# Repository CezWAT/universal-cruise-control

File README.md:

Universal cruise control for cars

# What it is
This project is about to bring cruise control to my Fiat 126p, but basically it should be possible to adapt it to any car.

# Sensors used
- hall sensor as a speed sensor
- brake light switch (already in place)
- clutch switch (has to be added)
- Three buttons (+, -, cancel)

# What is driving what
Based on the speed sensor, the device regulates PWM signal with PI loop. It tries to keep the vehicle speed as close as possible to the one set with the buttons. What controls the engine is a simple, but "strong" servomotor. In my case it is TiankongRC TD-6620MG (they say it has metal gears, 180 degrees of movement and 20 kg of torque). The servo is attached to gas pedal linkage as it is a simple connection and there are no vibrations on the floor compared to the engine.

# Where is the firmware
In FW directory. Be aware, that for now it is only a proof of concept made for HW v. 1. There are many functions that I would like to work but I didn't code it yet.

It's bare metal and I started writing it with HW v1, so I have to make some changes.

# Changes in HW between versions
v1:
- controls DC motor with H bridge. It came out as not so simple due to lack of motor position sensing.
- buttons and switches had to be debounced in code, this takes time and control over cruise control is somehow critical on the road.
- buttons were driven from the VCC.
- I misplaced pins in AMSR20783.3JZ footprint.

v2:
- improved misconceptions from above.
- JST connectors instead of goldpins.
- improved routing and footprints (for example SOT123 in place of SOT323 for improved solderability).

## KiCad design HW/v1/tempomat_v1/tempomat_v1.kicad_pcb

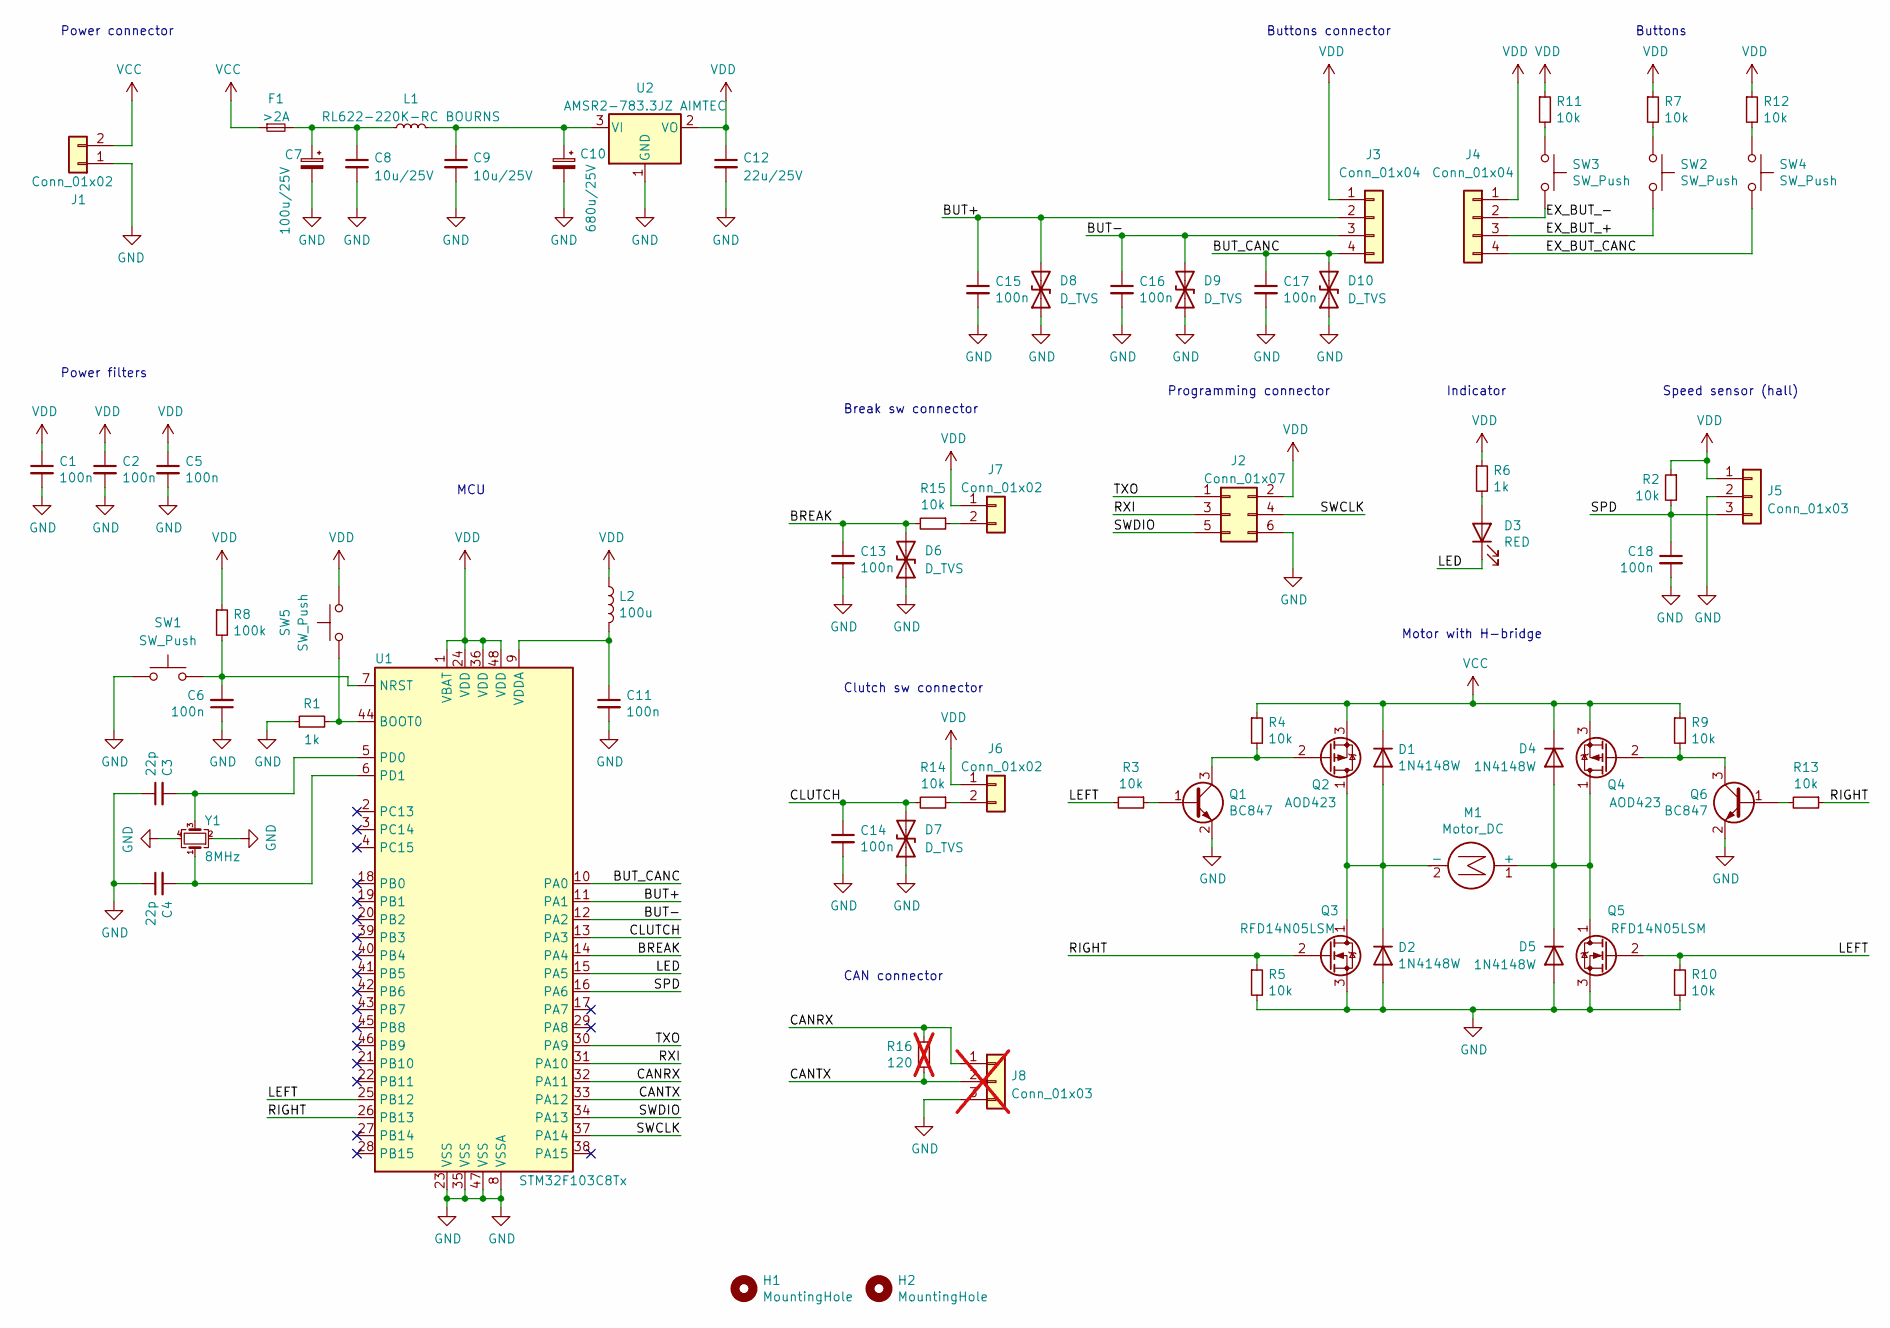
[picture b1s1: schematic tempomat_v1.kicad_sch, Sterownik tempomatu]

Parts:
C1, C2, C5, C6, C13, C14, C15, C16, C17, C18: 100n; C_0603_1608Metric
C3, C4: 22p; C_0603_1608Metric
C7: 100u/25V; CP_Radial_D5.0mm_P2.50mm
C8, C9: 10u/25V; C_1206_3216Metric
C10: 680u/25V; CP_Radial_D10.0mm_P5.00mm
C11: 100n; C_0603_1608Metric_Pad1.08x0.95mm_HandSolder
C12: 22u/25V; CP_Radial_D6.3mm_P2.50mm
D1, D2, D4, D5: 1N4148W; D_SOD-123
D3: RED; D_0603_1608Metric
D6, D7, D8, D9, D10: D_TVS; D_SOD-323_HandSoldering
F1: >2A; Fuse_0805_2012Metric
H1, H2: MountingHole; MountingHole_3.5mm
J1: Conn_01x02; TerminalBlock_bornier-2_P5.08mm
J2: Conn_01x07; PinHeader_2x03_P2.54mm_Vertical
J3, J4: Conn_01x04; PinHeader_1x04_P2.54mm_Vertical
J5: Conn_01x03; PinHeader_1x03_P2.54mm_Vertical
J6, J7: Conn_01x02; PinHeader_1x02_P2.54mm_Vertical
J8: Conn_01x03; PinHeader_1x03_P2.54mm_Vertical; not fitted
L1: RL622-220K-RC BOURNS; L_Radial_D8.7mm_P5.00mm_Fastron_07HCP
L2: 100u; L_1210_3225Metric_Pad1.42x2.65mm_HandSolder
M1: Motor_DC; PinHeader_1x02_P2.54mm_Vertical
Q1, Q6: BC847; SOT-23
Q2, Q4: AOD423; TO-252-3_TabPin1
Q3, Q5: RFD14N05LSM; TO-252-3_TabPin1
R1, R6: 1k; R_0603_1608Metric
R2, R3, R4, R5, R7, R9, R10, R11, R12, R13, R14, R15: 10k; R_0603_1608Metric
R8: 100k; R_0603_1608Metric
R16: 120; R_0603_1608Metric; not fitted
SW1, SW2, SW3, SW4, SW5: SW_Push; SW_PUSH_6mm
U1: STM32F103C8Tx; LQFP-48_7x7mm_P0.5mm
U2: AMSR2-783.3JZ AIMTEC; AMSR2-78JZ
Y1: 8MHz; Crystal_SMD_EuroQuartz_MJ-4Pin_5.0x3.2mm

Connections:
/BREAK: C13.1, D6.2 (A2), R15.2, U1.14 (PA4)
/BUT+: C15.1, D8.2 (A2), J3.2, U1.11 (PA1)
/BUT-: C16.1, D9.2 (A2), J3.3, U1.12 (PA2)
/BUT_CANC: C17.1, D10.2 (A2), J3.4, U1.10 (PA0)
/CANRX: J8.1, R16.1, U1.32 (PA11)
/CANTX: J8.2, R16.2, U1.33 (PA12)
/CLUTCH: C14.1, D7.2 (A2), R14.2, U1.13 (PA3)
/EX_BUT_+: J4.3, SW2.2
/EX_BUT_-: J4.2, SW3.2
/EX_BUT_CANC: J4.4, SW4.2
/LED: D3.1 (K), U1.15 (PA5)
/LEFT: Q5.2 (G), R3.2, R10.1, U1.25 (PB12)
/RIGHT: Q3.2 (G), R5.1, R13.1, U1.26 (PB13)
/RXI: J2.3, U1.31 (PA10)
/SPD: C18.1, J5.3, R2.2, U1.16 (PA6)
/SWCLK: J2.4, U1.37 (PA14)
/SWDIO: J2.5, U1.34 (PA13)
/TXO: J2.1, U1.30 (PA9)
GND: C1.2, C2.2, C3.1, C4.1, C5.2, C6.1, C7.2, C8.2, C9.2, C10.2, C11.2, C12.2, C13.2, C14.2, C15.2, C16.2, C17.2, C18.2, D2.2 (A), D5.2 (A), D6.1 (A1), D7.1 (A1), D8.1 (A1), D9.1 (A1), D10.1 (A1), J1.1, J2.6, J5.2, J8.3, Q1.2 (E), Q3.3 (S), Q5.3 (S), Q6.2 (E), R1.1, R5.2, R10.2, SW1.1, U1.8 (VSSA), U1.23 (VSS), U1.35 (VSS), U1.47 (VSS), U2.1 (GND), Y1.2, Y1.4
unnamed: C7.1, C8.1, F1.2, L1.1
unnamed: D1.2 (A), D2.1 (K), M1.2 (-), Q2.1 (D), Q3.1 (D)
unnamed: D3.2 (A), R6.2
unnamed: D4.2 (A), D5.1 (K), M1.1 (+), Q4.1 (D), Q5.1 (D)
unnamed: J6.2, R14.1
unnamed: J7.2, R15.1
unnamed: Q1.1 (B), R3.1
unnamed: Q1.3 (C), Q2.2 (G), R4.2
unnamed: Q4.2 (G), Q6.3 (C), R9.2
unnamed: Q6.1 (B), R13.2
unnamed: R7.2, SW2.1
unnamed: R11.2, SW3.1
unnamed: R12.2, SW4.1
unnamed: R1.2, SW5.2, U1.44 (BOOT0)
unnamed: C6.2, R8.2, SW1.2, U1.7 (NRST)
unnamed: C3.2, U1.5 (PD0), Y1.3
unnamed: C4.2, U1.6 (PD1), Y1.1
unnamed: C11.1, L2.2, U1.9 (VDDA)
unnamed: C9.1, C10.1, L1.2, U2.3 (VI)
VCC: D1.1 (K), D4.1 (K), F1.1, J1.2, Q2.3 (S), Q4.3 (S), R4.1, R9.1
VDD: C1.1, C2.1, C5.1, C12.1, J2.2, J3.1, J4.1, J5.1, J6.1, J7.1, L2.1, R2.1, R6.1, R7.1, R8.1, R11.1, R12.1, SW5.1, U1.1 (VBAT), U1.24 (VDD), U1.36 (VDD), U1.48 (VDD), U2.2 (VO)

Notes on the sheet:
Buttons
MCU
Programming connector
Buttons connector
Power connector
Clutch sw connector
Indicator
Power filters
Speed sensor (hall)
CAN connector
Break sw connector
Motor with H-bridge

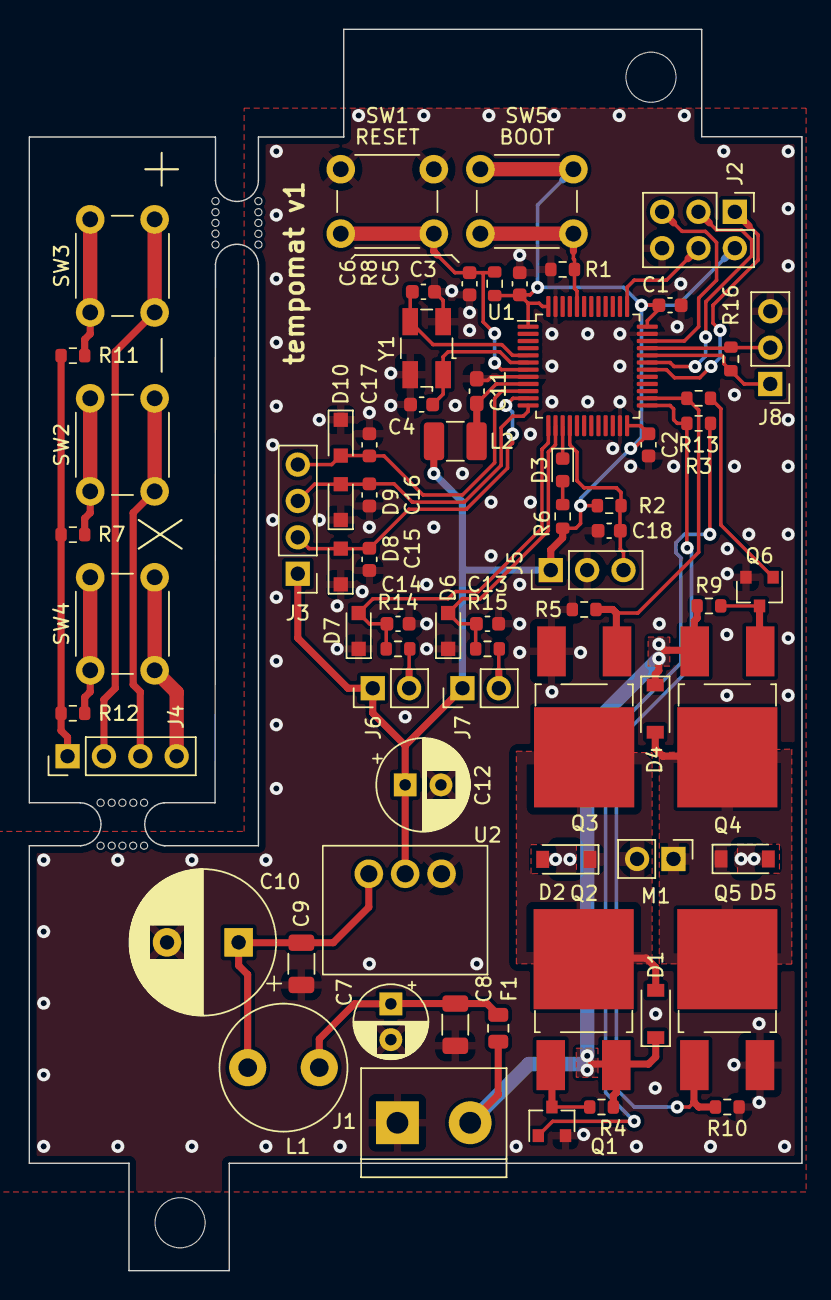
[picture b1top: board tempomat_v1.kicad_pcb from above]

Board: 2 copper layers, 54.0 x 86.7 mm, 74 parts (0 on the bottom side), 40 nets.

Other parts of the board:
mouse-bite-3mm-slot, mouse-bite-3mm-slot#2: VAL**; mouse-bite-3mm-slot

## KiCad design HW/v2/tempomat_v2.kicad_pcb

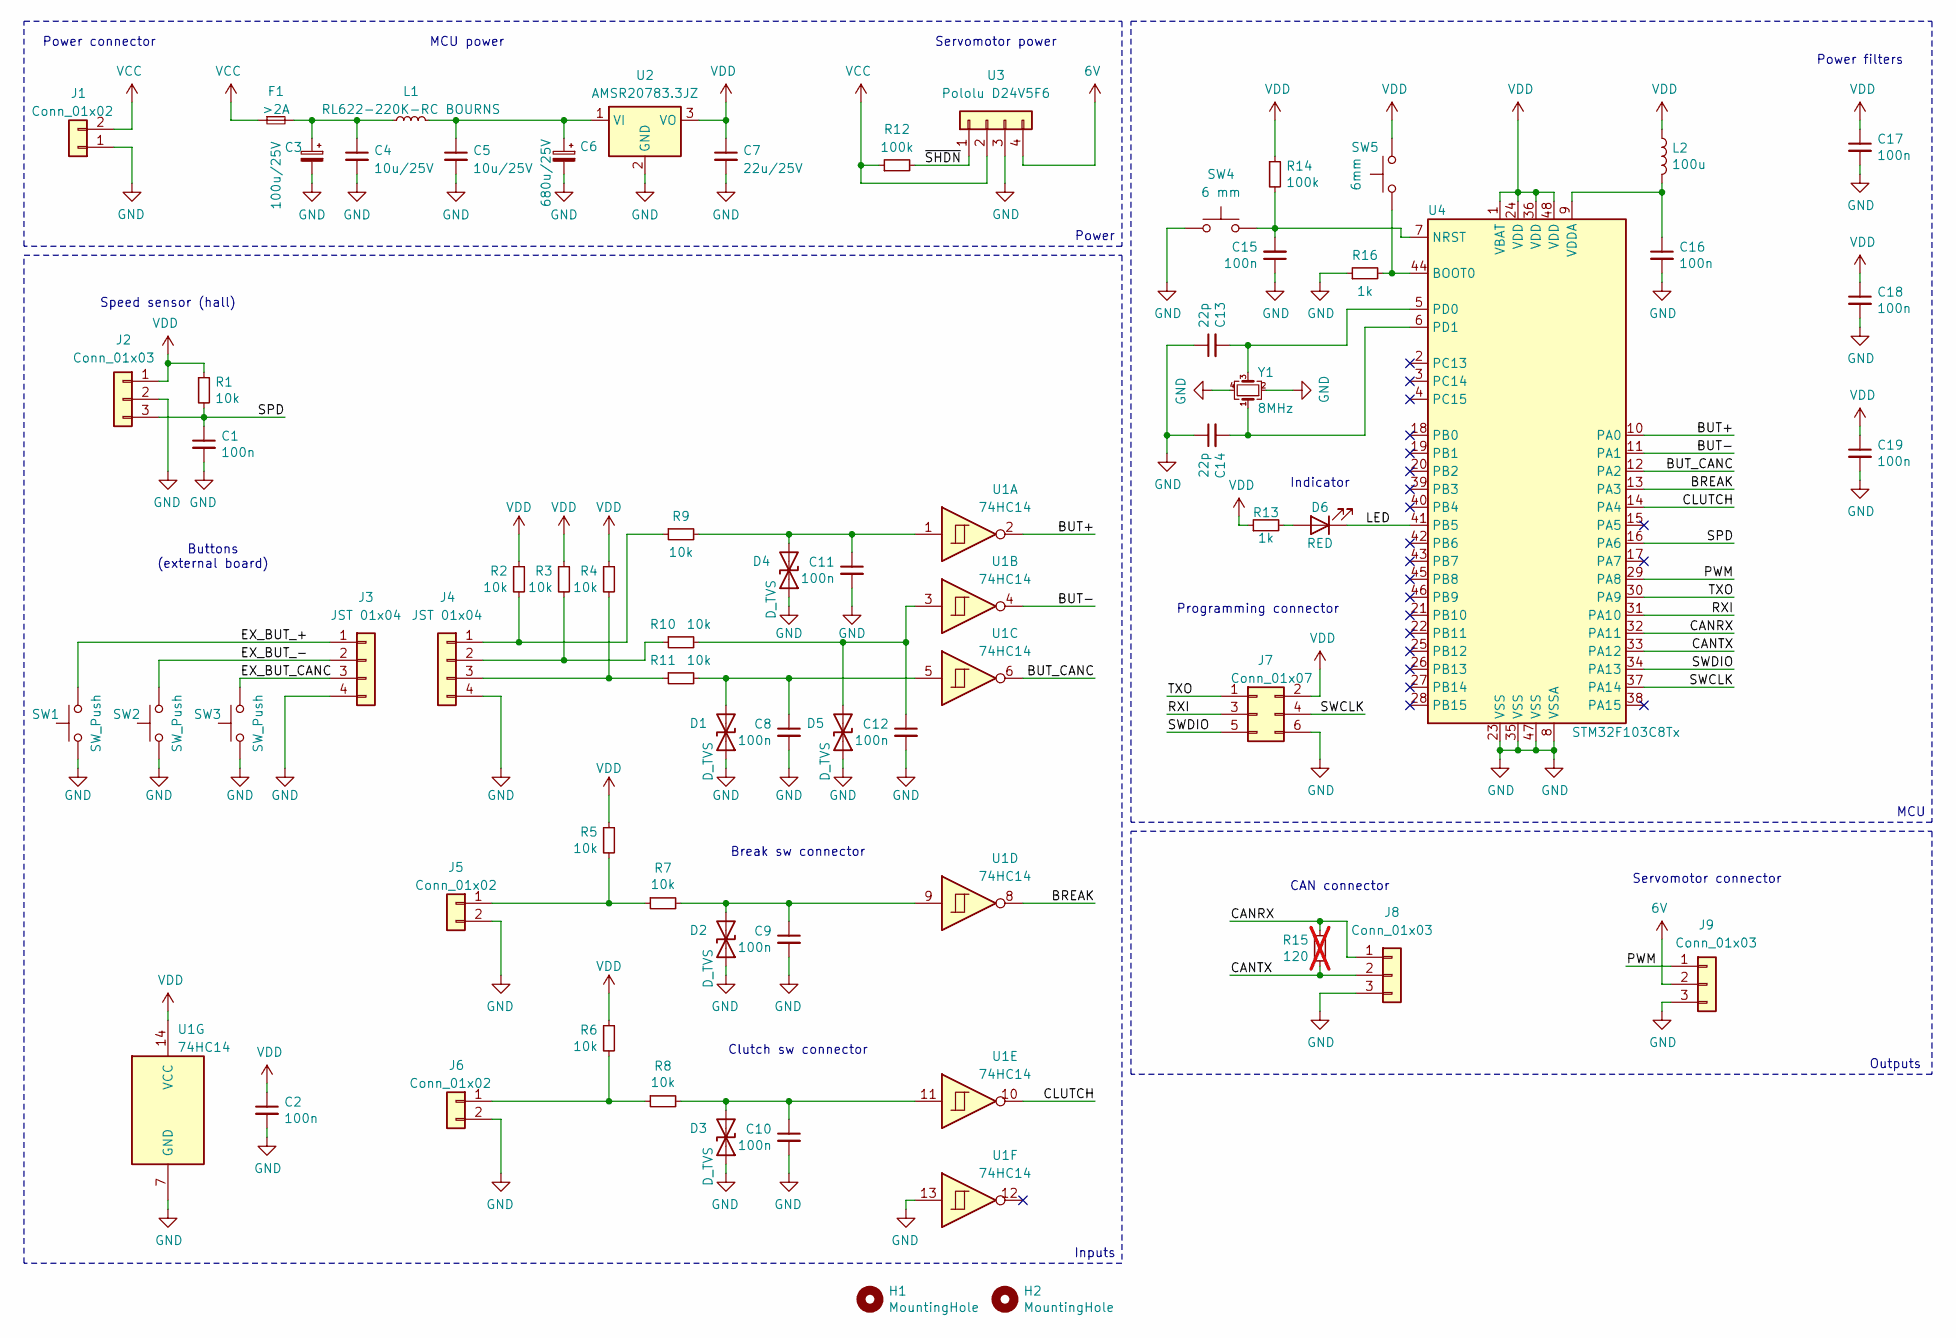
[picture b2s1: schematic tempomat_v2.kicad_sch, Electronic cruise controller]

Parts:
C1, C2, C8, C9, C10, C11, C12, C15, C17, C18, C19: 100n; C_0603_1608Metric
C3: 100u/25V; CP_Radial_D5.0mm_P2.50mm
C4, C5: 10u/25V; C_1206_3216Metric
C6: 680u/25V; CP_Radial_D10.0mm_P5.00mm
C7: 22u/25V; CP_Radial_D6.3mm_P2.50mm
C13, C14: 22p; C_0603_1608Metric
C16: 100n; C_0603_1608Metric_Pad1.08x0.95mm_HandSolder
D1, D2, D3, D4, D5: D_TVS; D_SOD-123
D6: RED; D_0603_1608Metric
F1: >2A; Fuse_0805_2012Metric
H1, H2: MountingHole; MountingHole_2.5mm
J1: Conn_01x02; TerminalBlock_bornier-2_P5.08mm
J2, J8, J9: Conn_01x03; JST_PH_B3B-PH-K_1x03_P2.00mm_Vertical
J3, J4: JST 01x04; JST_PH_B4B-PH-K_1x04_P2.00mm_Vertical
J5, J6: Conn_01x02; JST_PH_B2B-PH-K_1x02_P2.00mm_Vertical
J7: Conn_01x07; PinHeader_2x03_P2.54mm_Vertical
L1: RL622-220K-RC BOURNS; L_Radial_D8.7mm_P5.00mm_Fastron_07HCP
L2: 100u; L_1210_3225Metric_Pad1.42x2.65mm_HandSolder
R1, R2, R3, R4, R5, R6, R7, R8, R9, R10, R11: 10k; R_0603_1608Metric
R12, R14: 100k; R_0603_1608Metric
R13, R16: 1k; R_0603_1608Metric
R15: 120; R_0603_1608Metric; not fitted
SW1, SW2, SW3: SW_Push; SW_PUSH_6mm
SW4: 6 mm; SW_PUSH_6mm
SW5: 6mm; SW_PUSH_6mm
U1: 74HC14; SOIC-14_3.9x8.7mm_P1.27mm
U2: AMSR20783.3JZ; AMSR2-78JZ
U3: Pololu D24V5F6; PinHeader_1x04_P2.54mm_Vertical
U4: STM32F103C8Tx; LQFP-48_7x7mm_P0.5mm
Y1: 8MHz; Crystal_SMD_EuroQuartz_MJ-4Pin_5.0x3.2mm

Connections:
6V: J9.2, U3.4
/BREAK: U1.8, U4.13 (PA3)
/BUT+: U1.2, U4.10 (PA0)
/BUT-: U1.4, U4.11 (PA1)
/BUT_CANC: U1.6, U4.12 (PA2)
/CANRX: J8.1, R15.1, U4.32 (PA11)
/CANTX: J8.2, R15.2, U4.33 (PA12)
/CLUTCH: U1.10, U4.14 (PA4)
/EX_BUT_+: J3.1, SW1.2
/EX_BUT_-: J3.2, SW2.2
/EX_BUT_CANC: J3.3, SW3.2
/LED: D6.1 (K), U4.41 (PB5)
/PWM: J9.1, U4.29 (PA8)
/RXI: J7.3, U4.31 (PA10)
/SPD: C1.1, J2.3, R1.2, U4.16 (PA6)
/SWCLK: J7.4, U4.37 (PA14)
/SWDIO: J7.5, U4.34 (PA13)
/TXO: J7.1, U4.30 (PA9)
/~SHDN: R12.2, U3.1
GND: C1.2, C2.2, C3.2, C4.2, C5.2, C6.2, C7.2, C8.2, C9.2, C10.2, C11.2, C12.2, C13.1, C14.1, C15.1, C16.2, C17.2, C18.2, C19.2, D1.1 (A1), D2.1 (A1), D3.1 (A1), D4.1 (A1), D5.1 (A1), J1.1, J2.2, J3.4, J4.4, J5.2, J6.2, J7.6, J8.3, J9.3, R16.1, SW1.1, SW2.1, SW3.1, SW4.1, U1.7 (GND), U1.13, U2.2 (GND), U3.3, U4.8 (VSSA), U4.23 (VSS), U4.35 (VSS), U4.47 (VSS), Y1.2, Y1.4
unnamed: C3.1, C4.1, F1.2, L1.1
unnamed: C8.1, D1.2 (A2), R11.2, U1.5
unnamed: C9.1, D2.2 (A2), R7.2, U1.9
unnamed: C10.1, D3.2 (A2), R8.2, U1.11
unnamed: C11.1, D4.2 (A2), R9.2, U1.1
unnamed: C12.1, D5.2 (A2), R10.2, U1.3
unnamed: D6.2 (A), R13.2
unnamed: J4.1, R2.2, R9.1
unnamed: J4.2, R3.2, R10.1
unnamed: J4.3, R4.2, R11.1
unnamed: J5.1, R5.2, R7.1
unnamed: J6.1, R6.2, R8.1
unnamed: C5.1, C6.1, L1.2, U2.1 (VI)
unnamed: R16.2, SW5.2, U4.44 (BOOT0)
unnamed: C15.2, R14.2, SW4.2, U4.7 (NRST)
unnamed: C13.2, U4.5 (PD0), Y1.3
unnamed: C14.2, U4.6 (PD1), Y1.1
unnamed: C16.1, L2.2, U4.9 (VDDA)
VCC: F1.1, J1.2, R12.1, U3.2
VDD: C2.1, C7.1, C17.1, C18.1, C19.1, J2.1, J7.2, L2.1, R1.1, R2.1, R3.1, R4.1, R5.1, R6.1, R13.1, R14.1, SW5.1, U1.14 (VCC), U2.3 (VO), U4.1 (VBAT), U4.24 (VDD), U4.36 (VDD), U4.48 (VDD)

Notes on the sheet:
Inputs
Power
Buttons (external board)
Outputs
MCU
Programming connector
MCU power
Servomotor power
Servomotor connector
Power connector
Clutch sw connector
Indicator
Power filters
Speed sensor (hall)
CAN connector
Break sw connector

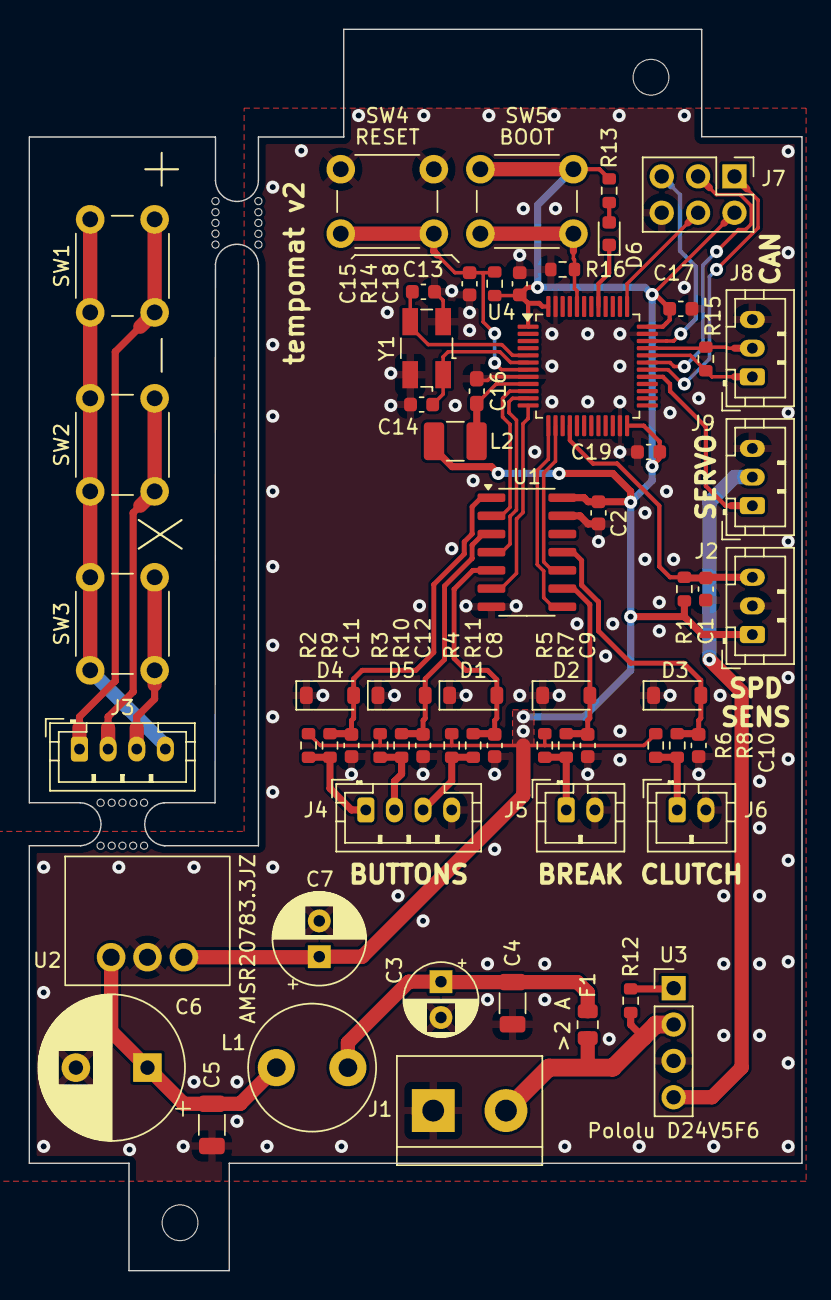
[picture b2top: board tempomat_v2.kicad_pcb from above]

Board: 2 copper layers, 54.0 x 86.7 mm, 67 parts (0 on the bottom side), 40 nets.

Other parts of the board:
mouse-bite-3mm-slot, mouse-bite-3mm-slot#2: VAL**; mouse-bite-3mm-slot

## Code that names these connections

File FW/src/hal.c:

#include "stm32f10x.h"
#include "main.h"
#include "hal.h"
#include "printf.h"

volatile uint8_t g_tim_speed_flag = 0;

void set_motor(uint16_t pwm)
{
	if (pwm >= PI_MIN && pwm <= PI_MAX)
	{
		TIM1->CCR4 = pwm;
	}
	else
	{
		TIM1->CCR4 = PI_MIN;
	}
	g_tim_speed_flag = 0;
}


uint8_t multiclick_buttons(uint8_t pin)
{
	extern uint8_t click_count;
	extern uint32_t last_click_time;

	if (gpio_read(pin))
	{
		if (click_count == 0)
		{
			// first click
			click_count++;
			last_click_time = g_time_tick;
		}
		else if (click_count == 1 && (g_time_tick - last_click_time) <= DOUBLE_CLICK_TIME)
		{
			// double click
			click_count = 0;
			return 2;
		}
	}
	else
	{
		if (click_count == 1 && (g_time_tick - last_click_time) > DOUBLE_CLICK_TIME)
		{
			// single click
			click_count = 0;
			return 1;
		}
	}
	return 0;
}


uint8_t gpio_read(uint8_t gpio)
{
	uint8_t pressed = GPIOA->IDR & (1 << gpio);
	return pressed;
}


static void disable_interrupts(void)
{
	__set_PRIMASK(1);
}


static void enable_interrupts(void)
{
	__set_PRIMASK(0);
}


void watchdog_feed(void)
{
	disable_interrupts();
	IWDG->KR |= IWDG_REFRESH;
	enable_interrupts();
}


void simple_putchar(char message)
{
	USART1->DR = message; // fill the buffer with message
	while ((USART1->SR & USART_SR_TC) == 0); // wait until transfer complete
}


static void gpio_init(void)
{
	RCC->APB2ENR |= RCC_APB2ENR_IOPAEN | RCC_APB2ENR_IOPBEN;
	RCC->APB1ENR |= RCC_APB1ENR_TIM3EN;
	RCC->APB2ENR |= RCC_APB2ENR_AFIOEN;

	// BUT_CANC (PA0)
	GPIOA->CRL &= ~GPIO_CRL_CNF0_0;
	GPIOA->CRL |= GPIO_CRL_CNF0_1;
	// GPIOA->ODR &= ~GPIO_ODR_ODR0; // floating input to pull-down

	// BUT+ (PA1)
	GPIOA->CRL &= ~GPIO_CRL_CNF1_0; // floating input to pull-down
	GPIOA->CRL |= GPIO_CRL_CNF1_1;

	// BUT- (PA2)
	GPIOA->CRL &= ~GPIO_CRL_CNF2_0; // floating input to pull-down
	GPIOA->CRL |= GPIO_CRL_CNF2_1;

	// CLUTCH (PA3)
	GPIOA->CRL &= ~GPIO_CRL_CNF3_0; // floating input to pull-down
	GPIOA->CRL |= GPIO_CRL_CNF3_1;

	// BREAK (PA4)
	GPIOA->CRL &= ~GPIO_CRL_CNF4_0; // floating input to pull-down
	GPIOA->CRL |= GPIO_CRL_CNF4_1;

	// SPD (PA6)
	// floating input - reset state

	// LED (PA5)
	GPIOA->CRL &=  ~(GPIO_CRL_CNF5_0 | GPIO_CRL_CNF5_1);
	GPIOA->CRL |= GPIO_CRL_MODE5_1; // set as output, max 2 MHz

	// UART
	// UART_TXO (PA9)
	GPIOA->CRH &= ~(GPIO_CRH_CNF9_0);
	GPIOA->CRH |= GPIO_CRH_CNF9_1;
	GPIOA->CRH |= GPIO_CRH_MODE9_1 | GPIO_CRH_MODE9_0;

	// UART_RXI (PA10) floating input - reset state

	// TIM1 (PA11)
	GPIOA->CRH &= ~(GPIO_CRH_CNF11  | GPIO_CRH_MODE11);
	GPIOA->CRH |= (GPIO_CRH_MODE11_1 | GPIO_CRH_MODE11_1); // set as output, max 50 MHz
	GPIOA->CRH &= ~GPIO_CRH_CNF11_0; // set push-pull AF
	GPIOA->CRH |= GPIO_CRH_CNF11_1; // set push-pull AF

	// SPEED CONTROL
	// LEFT (PB12)
	GPIOB->CRH &= ~(GPIO_CRH_CNF12_0 | GPIO_CRH_CNF12_1);
	GPIOB->CRH |= GPIO_CRH_MODE12_1; // set as output, max 2 MHz

	// RIGHT (PB13)
	GPIOB->CRH &= ~(GPIO_CRH_CNF13_0 | GPIO_CRH_CNF13_1);
	GPIOB->CRH |= GPIO_CRH_MODE13_1; // set as output, max 2 MHz
}


// Set Timer 1 for setting motor position, PWM
static void timer_1_init(void)
{
	#define PRESCALE (SystemCoreClock / PRESCALE_1MHZ)
	#define PERIOD (SystemCoreClock / PRESCALE / PULSE_FREQ)
	RCC->APB2ENR |= RCC_APB2ENR_TIM1EN;
	TIM1->PSC = PRESCALE;
	TIM1->ARR = PERIOD; // PWM frequency
	TIM1->CCR4 = PI_MIN; // PWM duty cycle <---  270 ... 2390 --->
	TIM1->CCMR2 &= ~(TIM_CCMR2_CC4S_0 | TIM_CCMR2_CC4S_1); // CC4 as output
	TIM1->CCMR2 |= (TIM_CCMR2_OC4M_1 | TIM_CCMR2_OC4M_2); // PWM Mode 1
	TIM1->CCMR2 |= TIM_CCMR2_OC4PE; // preload enable
	TIM1->CR1 |= TIM_CR1_ARPE; // auto-reload preload
	TIM1->EGR |= TIM_EGR_UG; // init all previous settings
	TIM1->CCER |= TIM_CCER_CC4E;
	TIM1->BDTR |= TIM_BDTR_MOE; // main output enable
	TIM1->CR1 |= TIM_CR1_CEN;
}


// Set Timer 3 for speed measurement
static void timer_3_init(void)
{
	TIM3->CCER &= ~TIM_CCER_CC1E;
	TIM3->CR2 &= ~TIM_CR2_TI1S; // make sure it is TI1
	TIM3->CCMR1 &= ~TIM_CCMR1_CC1S_1; // make sure to zero out CC1S_1
	TIM3->CCMR1 |= TIM_CCMR1_CC1S_0 | TIM_CCMR1_IC1F_2; // select Capture 1 | filter 2
	TIM3->CCER &= ~TIM_CCER_CC1P & ~TIM_CCER_CC1NP;
	TIM3->CCER |= TIM_CCER_CC1E; // enable Capture input
	TIM3->PSC = PRESCALE_TMR3;
	TIM3->EGR |= TIM_EGR_UG;
	TIM3->DIER |= TIM_DIER_CC1IE | TIM_DIER_UIE; // interrupt
	TIM3->CR1 |= TIM_CR1_CEN;
	NVIC_EnableIRQ(TIM3_IRQn);
}


static void watchdog_init(void)
{
	RCC->APB1ENR |= RCC_APB1ENR_WWDGEN;
	IWDG->KR |= IWDG_EN;
	IWDG->PR |= IWDG_PRESCALER;
	IWDG->KR |= IWDG_REFRESH;
}


// configure USART1 for baudrate 115200, 8N1, FIFO
static void usart1_init(void)
{
	RCC->APB2ENR |= RCC_APB2ENR_USART1EN;
	USART1->BRR = UART_BAUD;
	USART1->CR1 |= USART_CR1_RE | USART_CR1_TE | USART_CR1_UE;
}


// use HSE clock
static void sysclk_init(void)
{
	RCC->CR |= RCC_CR_HSEON;
	RCC->CFGR = RCC_CFGR_SW_HSE;
	SystemCoreClockUpdate();
}


// execute initializations of all used peripherals
void init(void)
{
	sysclk_init();
	gpio_init();
	watchdog_init();
	timer_1_init(); // setting motor position
	timer_3_init(); // measurement
	usart1_init(); // UART
	SysTick_Config(SYSTICK_DELAY);

	simple_printf("Init done\r\n");
}


__attribute__((section(".after_vectors"))) void TIM1_IRQHandler()
{
	g_tim_speed_flag = 1;
}


__attribute__((section(".after_vectors"))) void HardFault_Handler()
{
	uint32_t lr = 0;
	__asm("MOV %0, LR\n" : "=r" (lr));
	uint32_t pc = 0;
	__asm("MOV %0, PC\n" : "=r" (pc));

	simple_printf("\tR0 (MSP): %x\r\n", __get_MSP());
	simple_printf("\tLR: %x\r\n", lr);
	simple_printf("\tPC: %x\r\n", pc);
	simple_printf("\txPSR: %x\r\n", __get_xPSR());
	simple_printf("\tAPSR: %x\r\n", __get_APSR());
	simple_printf("\tIPSR: %x, Exception: Hard Fault\r\n", __get_IPSR());

	NVIC_SystemReset();
}


__attribute__((section(".after_vectors"))) void SysTick_Handler()
{
	g_time_tick++;
}

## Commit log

2024-09-04 Add HW version 1 & 2
2024-09-04 add license, add manual testing tool based on arduino
2024-09-10 [WIP] FW for HW v. 1.; A good starting point for HW v. 2.
2025-02-05 Add double button press + button fixes
